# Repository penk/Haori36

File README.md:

# Haori36

Low-pro 36-key hot-swappable monoblock split ortho keyboard with optional Pimoroni trackball support. 

## Production Files

To place an order for the Haori36 PCB: 

- Use the gerber files in the [production/](production/) folder. 
- Optionally one can utilize the [BOM](production/BOM.csv) and [CPL](production/CPL.csv) files with a PCBA service to avoid manually soldering SMD diodes, which can be challenging to solder by hand. All components are soldered to the bottom side of the board. 

The complete PCB project is in the [kicad/](kicad/) folder. 

## Bill of Materials (BOM)

Quantity | Item 
--- | --- 
1 | RP2040-Zero & Pin headers 
1 | Haori36 PCB 
1 | Haori36 plate 
36 | Kailh Choc V1 switches  
36 | Kailh Choc V1 Hot-swap sockets 
36 | 1N4148 diodes (SMD)
1 | Pimoroni Trackball Breakout (optional)
4 | M2x4 heat-set thread inserts
4 | M2x6 screws 

## Case and Plate 

3D print the case with the [STL file](case/haori36-case.stl). 

|  |  |
|---|---|

There are multiple options for the plate:

- 3D print using the [STL file](plate/haori36-plate.stl) (or the [no-trackball](plate/haori36-plate-notrakball.stl) version).
    - Adjust the tolerance settings as needed. As a reference, I set the `Initial Layer Horizontal Expansion` to `-0.3mm` and the `Horizontal Expansion` for subsequent layers to `-0.1mm`.
- Use PCB material with the [plate gerber files](production/haori36-plate-gerbers.zip), and opt for `1.6mm` or `2.0mm` PCB thickness. 
- Laser cut with the [DXF file](plate/haori36-plate.dxf).

The folder also contains an editable [STEP file](case/Haori36-case.step) for customization. 

## Firmware 

The Haori36 comes with precompiled VIA-enabled firmware, with trackball enabled by default: 

- Flash [penk_haori36_via.uf2](firmware/penk_haori36_via.uf2) to the RP2040-Zero.
- Load the [via.json](firmware/QMK/via.json) file in `Design` tab for [VIA](https://usevia.app) configuration.

### Default Keymaps

The firmware source is located under [firmware/QMK/](firmware/QMK/). 
The trackball settings can be adjusted in [rules.mk](firmware/QMK/keymaps/via/rules.mk) and [config.h](firmware/QMK/keymaps/via/config.h). 

## Copyright and License
Copyright (c) 2024 Penk Chen. All rights reserved.

All files are licensed under MIT license, see the [LICENSE](LICENSE) for more information.

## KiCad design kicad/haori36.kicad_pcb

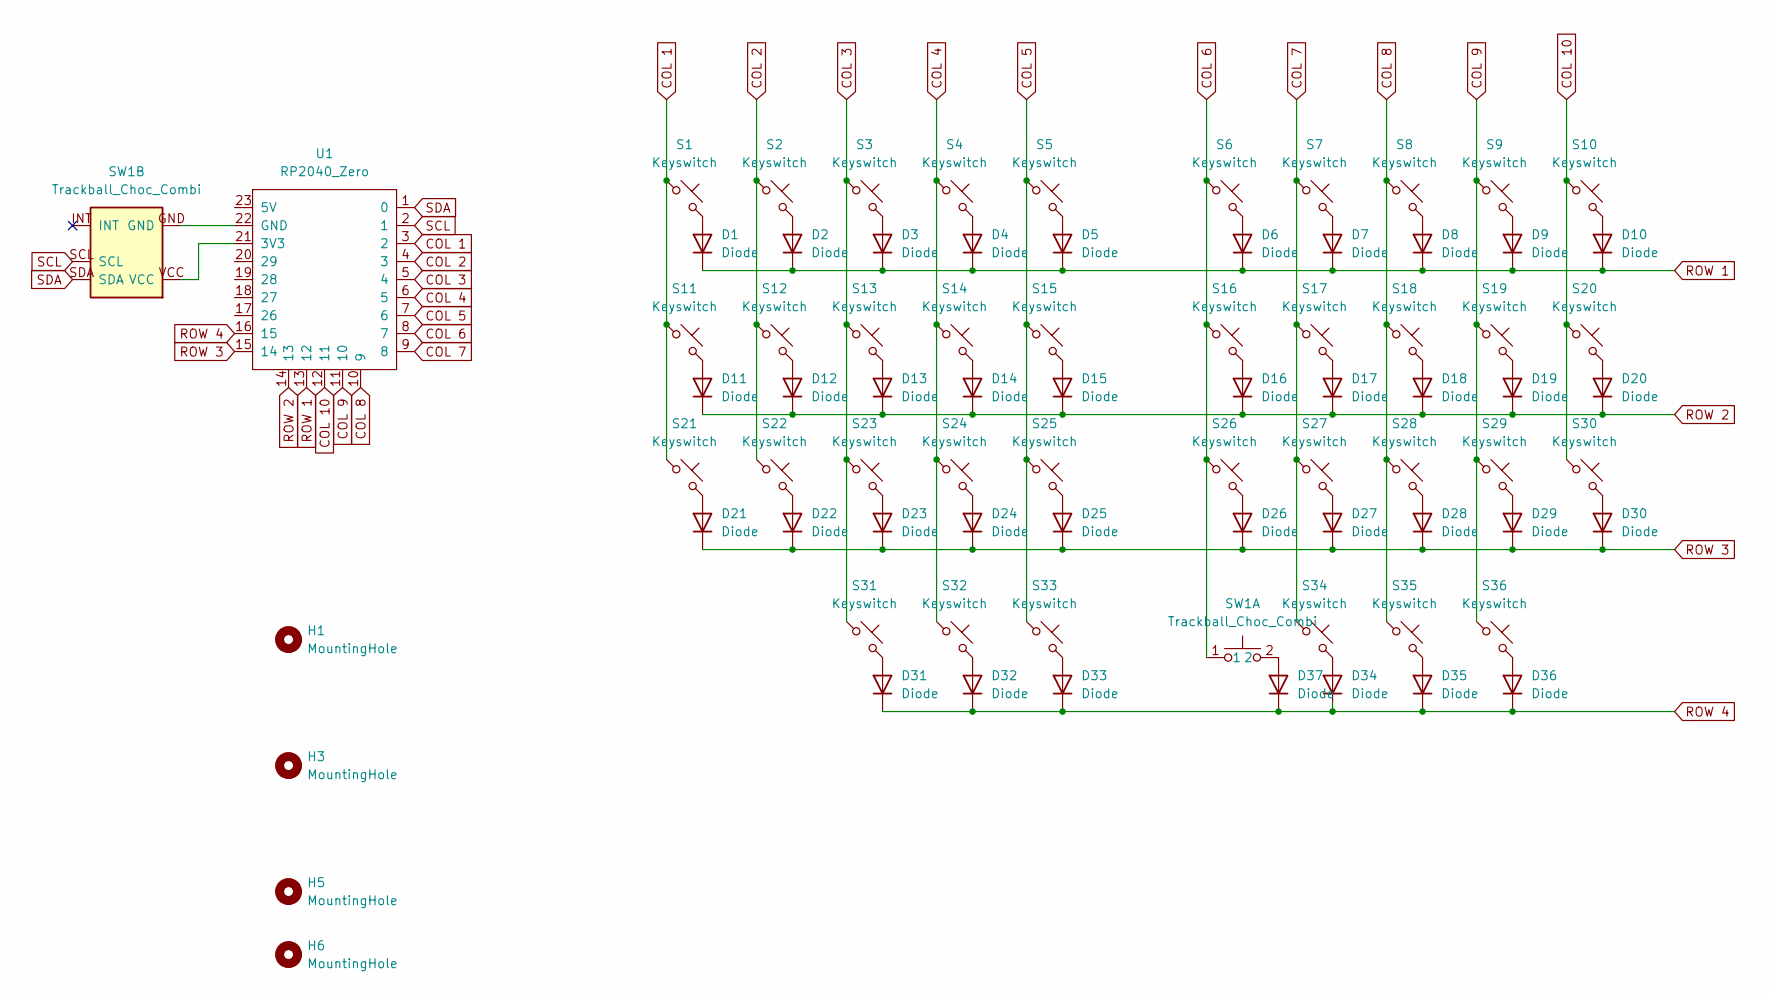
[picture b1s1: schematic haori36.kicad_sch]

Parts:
D1, D2, D3, D4, D5, D6, D7, D8, D9, D10, D11, D12, D13, D14, D15, D16, D17, D18, D19, D20, D21, D22, D23, D24, D25, D26, D27, D28, D29, D30, D31, D32, D33, D34, D35, D36, D37: Diode; Diode_SOD-123
H1, H3, H5, H6: MountingHole; MountingHole_2.2mm_M2
S1, S2, S3, S4, S5, S6, S7, S8, S9, S10, S11, S12, S13, S14, S15, S16, S17, S18, S19, S20, S21, S22, S23, S24, S25, S26, S27, S28, S29, S30, S31, S32, S33, S34, S35, S36: Keyswitch; SW_choc_v1_HS_1u
SW1: Trackball_Choc_Combi; trackball_choc_combi
U1: RP2040_Zero

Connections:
COL 1: S1.1, S11.1, S21.1, U1.3 (2)
COL 2: S2.1, S12.1, S22.1, U1.4 (3)
COL 3: S3.1, S13.1, S23.1, S31.1, U1.5 (4)
COL 4: S4.1, S14.1, S24.1, S32.1, U1.6 (5)
COL 5: S5.1, S15.1, S25.1, S33.1, U1.7 (6)
COL 6: S6.1, S16.1, S26.1, SW1.1, U1.8 (7)
COL 7: S7.1, S17.1, S27.1, S34.1, U1.9 (8)
COL 8: S8.1, S18.1, S28.1, S35.1, U1.10 (9)
COL 9: S9.1, S19.1, S29.1, S36.1, U1.11 (10)
COL 10: S10.1, S20.1, S30.1, U1.12 (11)
unnamed: D1.2 (A), S1.2
unnamed: D2.2 (A), S2.2
unnamed: D3.2 (A), S3.2
unnamed: D4.2 (A), S4.2
unnamed: D5.2 (A), S5.2
unnamed: D6.2 (A), S6.2
unnamed: D7.2 (A), S7.2
unnamed: D8.2 (A), S8.2
unnamed: D9.2 (A), S9.2
unnamed: D10.2 (A), S10.2
unnamed: D11.2 (A), S11.2
unnamed: D12.2 (A), S12.2
unnamed: D13.2 (A), S13.2
unnamed: D14.2 (A), S14.2
unnamed: D15.2 (A), S15.2
unnamed: D16.2 (A), S16.2
unnamed: D17.2 (A), S17.2
unnamed: D18.2 (A), S18.2
unnamed: D19.2 (A), S19.2
unnamed: D20.2 (A), S20.2
unnamed: D21.2 (A), S21.2
unnamed: D22.2 (A), S22.2
unnamed: D23.2 (A), S23.2
unnamed: D24.2 (A), S24.2
unnamed: D25.2 (A), S25.2
unnamed: D26.2 (A), S26.2
unnamed: D27.2 (A), S27.2
unnamed: D28.2 (A), S28.2
unnamed: D29.2 (A), S29.2
unnamed: D30.2 (A), S30.2
unnamed: D31.2 (A), S31.2
unnamed: D32.2 (A), S32.2
unnamed: D33.2 (A), S33.2
unnamed: D34.2 (A), S34.2
unnamed: D35.2 (A), S35.2
unnamed: D36.2 (A), S36.2
unnamed: D37.2 (A), SW1.2
unnamed: SW1.VCC, U1.21 (3V3)
unnamed: SW1.GND, U1.22 (GND)
ROW 1: D1.1 (K), D2.1 (K), D3.1 (K), D4.1 (K), D5.1 (K), D6.1 (K), D7.1 (K), D8.1 (K), D9.1 (K), D10.1 (K), U1.13 (12)
ROW 2: D11.1 (K), D12.1 (K), D13.1 (K), D14.1 (K), D15.1 (K), D16.1 (K), D17.1 (K), D18.1 (K), D19.1 (K), D20.1 (K), U1.14 (13)
ROW 3: D21.1 (K), D22.1 (K), D23.1 (K), D24.1 (K), D25.1 (K), D26.1 (K), D27.1 (K), D28.1 (K), D29.1 (K), D30.1 (K), U1.15 (14)
ROW 4: D31.1 (K), D32.1 (K), D33.1 (K), D34.1 (K), D35.1 (K), D36.1 (K), D37.1 (K), U1.16 (15)
SCL: SW1.SCL, U1.2 (1)
SDA: SW1.SDA, U1.1 (0)

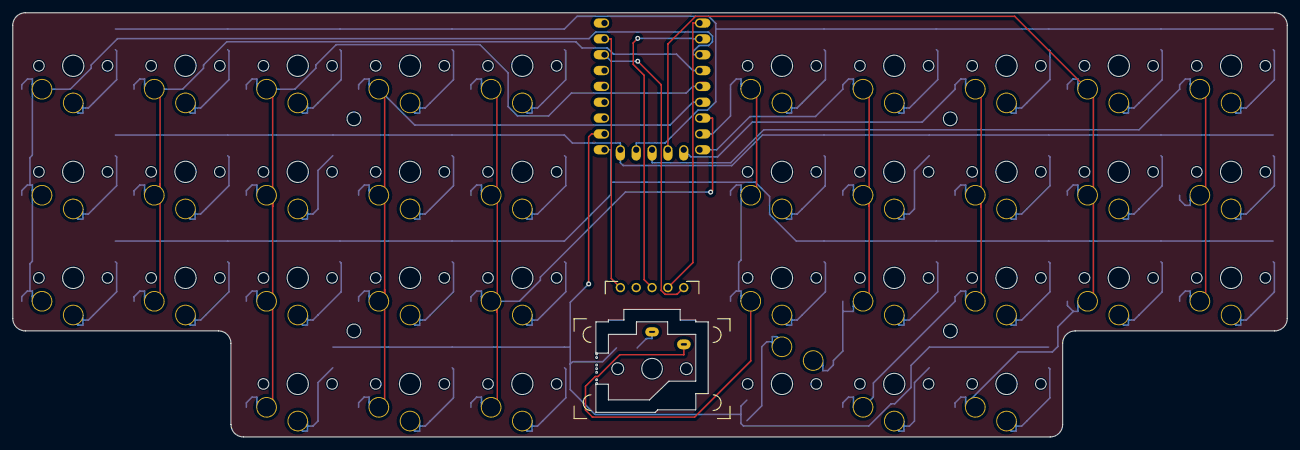
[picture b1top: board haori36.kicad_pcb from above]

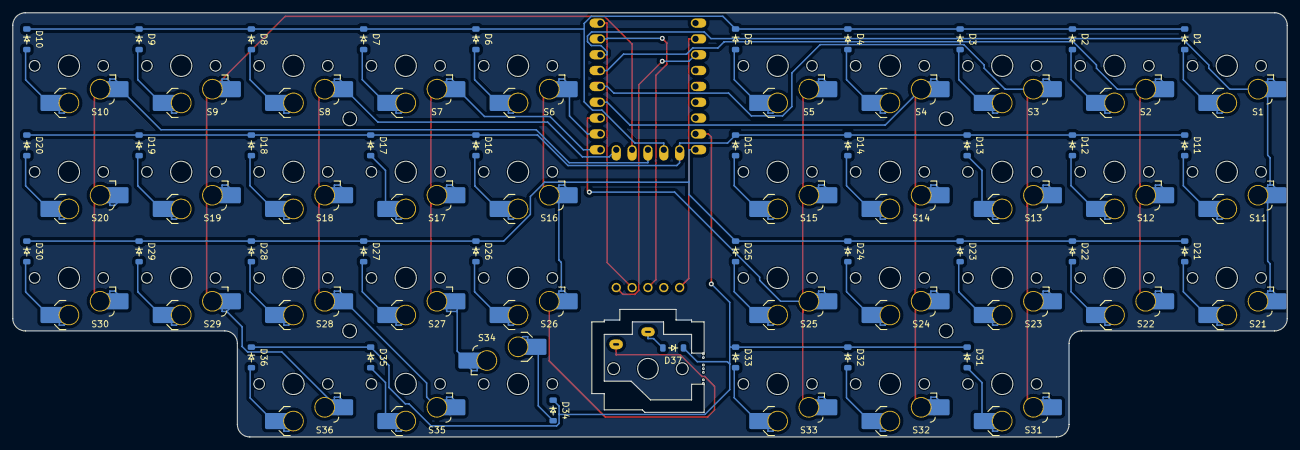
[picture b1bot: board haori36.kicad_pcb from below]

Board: 2 copper layers, 204.3 x 68.0 mm, 79 parts (73 on the bottom side), 55 nets.

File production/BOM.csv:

Designator,Footprint,Quantity,Value,LCSC Part #
"D1, D10, D11, D12, D13, D14, D15, D16, D17, D18, D19, D2, D20, D21, D22, D23, D24, D25, D26, D27, D28, D29, D3, D30, D31, D32, D33, D34, D35, D36, D37, D4, D5, D6, D7, D8, D9",Diode_SOD-123,37,Diode,
"S1, S10, S11, S12, S13, S14, S15, S16, S17, S18, S19, S2, S20, S21, S22, S23, S24, S25, S26, S27, S28, S29, S3, S30, S31, S32, S33, S34, S35, S36, S4, S5, S6, S7, S8, S9",SW_choc_v1_HS_1u,36,Keyswitch,

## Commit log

2024-03-14 Update keymaps
2024-03-14 Update README and images
2024-04-18 Update case and keymaps
